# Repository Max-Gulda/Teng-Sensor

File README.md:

# TENG Sensor Scope

This repository contains two parts:

- `nrf54/`: Zephyr firmware for the Nordic **nRF54L15 DK target** (`nrf54l15dk/nrf54l15/cpuapp`) used by the course board setup
- `gui/`: a Python BLE scope GUI that displays calibrated ADS131M04 voltage streams

Minimal Zephyr RTOS firmware intended for the course proprietary board setup. The Zephyr build target used for this course setup is:

- `nrf54l15dk/nrf54l15/cpuapp`

The firmware samples **ADS131M04** 24-bit ADC data. All 4 ADC channels are enabled and streamed over BLE as signed raw counts. CH0 and CH1 are intended to be displayed as source voltage through the 100k/15k input dividers; CH2 and CH3 are direct ADC input voltage.

It transmits data over **Bluetooth LE** using custom GATT characteristics plus Nordic UART Service (NUS) for logs and scope commands.

## Attribution

Created by:

- **Jesper Sjöberg** — GitHub: [@repsejs](https://github.com/repsejs) — KTH: **@jessjobe**
- **Max Gulda** — GitHub: [@Max-Gulda](https://github.com/Max-Gulda) — KTH: **@gulda**

## Architecture

### Threads and priorities

| Thread | Priority | What it does | Key code |
|---|---:|---|---|
| Sampling | 5 | Reads ADC on ADS131M04 DRDY falling edges and queues data to BLE | `nrf54/src/sampling/sampling.c` |
| Bluetooth | 7 | Batches and transmits ADC notifications; manages connect/disconnect | `nrf54/src/bluetooth/bluetooth.c`, `nrf54/src/bluetooth/bt_*.c` |
| Main | default | Initialization + periodic CPU load logging | `nrf54/src/main.c` |

### Data flow

```text
ADS131M04 CH0-CH3 ─► sampling_thread ───────────────────────────────────────────────► BLE ADC channel (batched notifications)
LOG_* / printk ─────────────────────────────► NUS (BLE log backend)
```

### Source layout (firmware)

- `nrf54/src/ads131m04_spi/` — ADS131M04 SPI driver + configuration
- `nrf54/src/sampling/` — DRDY-driven sampling thread, queues ADC frames to BLE
- `nrf54/src/bluetooth/` — BLE GATT services, batching, queues, and notifications
- `nrf54/src/ble_log_backend/` — routes Zephyr `LOG_*` output over BLE (NUS)

### ADS131M04 notes

- The old `ads131m02_spi` module was renamed to `ads131m04_spi`.
- The driver parses 4 ADC channels and exposes CH0, CH1, CH2, and CH3 in `ads131m04_data_t`.
- The default setup in `ads131m04_full_setup()` enables all four channels.
- CH0 and CH1 have 100k/15k dividers and are converted to source voltage in the GUI.
- CH2 and CH3 have no divider and are converted to direct ADC input voltage in the GUI.
- The main custom BLE ADC payload carries timestamp + CH0 + CH1 + CH2 + CH3.
- Sampling is driven by the ADS131M04 DRDY pin. The default ADC OSR is 8192 (500 SPS), and the GUI can switch among the standard ADS131M04 output data rates.

## Build and run (VS Code + nRF Connect extension)

### Important (VS Code workspace)

When using the **nRF Connect for VS Code** extension, make sure the **opened workspace folder is `nrf54/`** (not the repo root). Otherwise the extension may not detect the application correctly.

### Prerequisites

- VS Code
- **nRF Connect for VS Code** extension installed (Nordic Semiconductor)
- A working nRF Connect SDK toolchain (the extension can install/manage this)
- The **course proprietary board** connected over USB (uses the nRF54L15 DK target)

### Open the project

1. Open this folder in VS Code.
2. In the nRF Connect sidebar:
   - Select the **application**: `nrf54/`
   - Select the board: `nrf54l15dk/nrf54l15/cpuapp`.

### Build

Use the nRF Connect extension’s **Build** action. This project uses Zephyr sysbuild (MCUboot enabled), matching:

```bash
cd nrf54
west build -b nrf54l15dk/nrf54l15/cpuapp --sysbuild
```

### Flash

Use the nRF Connect extension’s **Flash** action, or from a terminal:

```bash
west flash
```

### View logs / verify it runs

You have two common options:

- **UART/serial logs**: use the extension’s serial monitor, or:

```bash
west espresso
```

- **BLE logs over NUS**: connect with a NUS-capable client and view logs streamed by the BLE log backend (enabled in `nrf54/src/main.c`).

## IntelliSense note (students)

This repo is configured to work with VS Code’s **C/C++ IntelliSense**. For full, correct include paths/macros, build once so Zephyr generates:

- `nrf54/build/compile_commands.json`

After the first build, IntelliSense should work.

## Bluetooth DFU (nRF Device Manager)

After building, the build directory will contain a DFU package:

- `nrf54/build/dfu_application.zip`

To flash **over Bluetooth** using the **nRF Device Manager** mobile app:

1. Flash once over USB initially (so the device has the bootloader + BLE DFU enabled).
2. Power the device and connect to it in **nRF Device Manager**.
3. Choose **DFU / Update firmware** (wording varies by app version).
4. Select `dfu_application.zip` and start the update.
5. Wait for the device to reboot and reconnect.

## GUI (Python)

To run the BLE scope GUI:

```bash
cd gui
uv sync
uv run teng-sensor-scope
```

Use **Settings** in the GUI to choose visible channels and plot window length.

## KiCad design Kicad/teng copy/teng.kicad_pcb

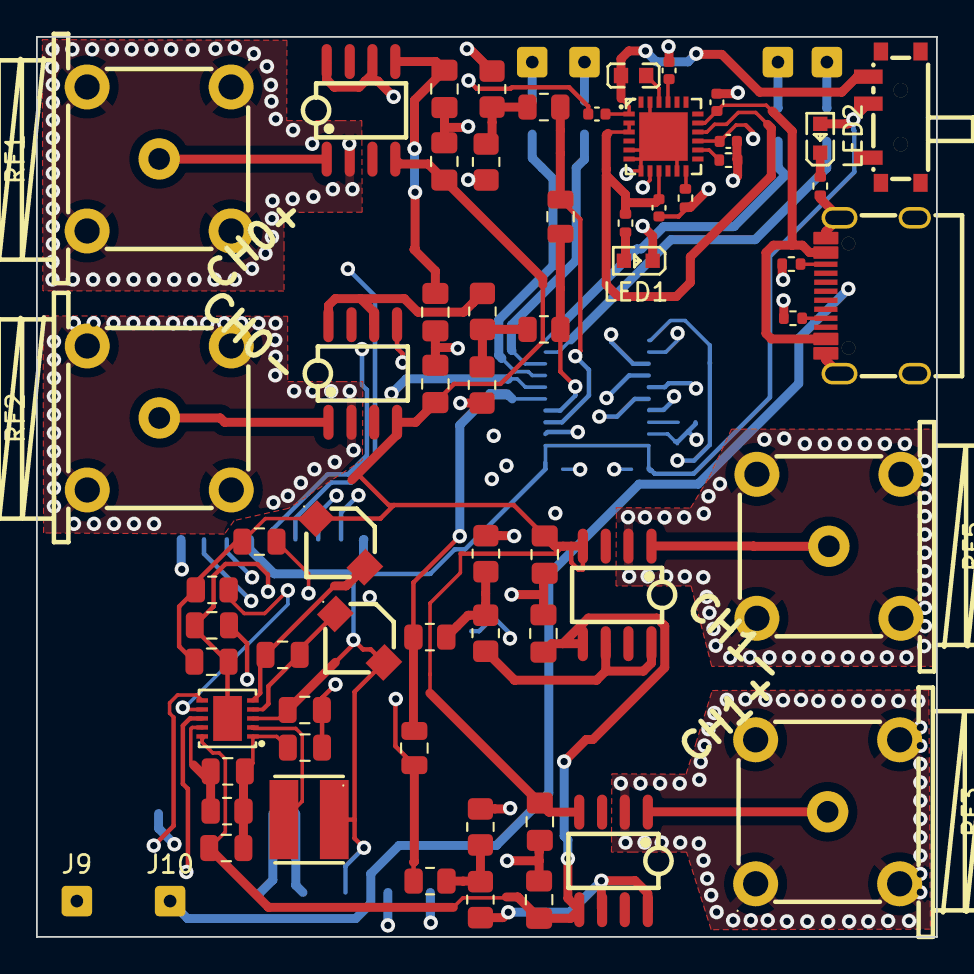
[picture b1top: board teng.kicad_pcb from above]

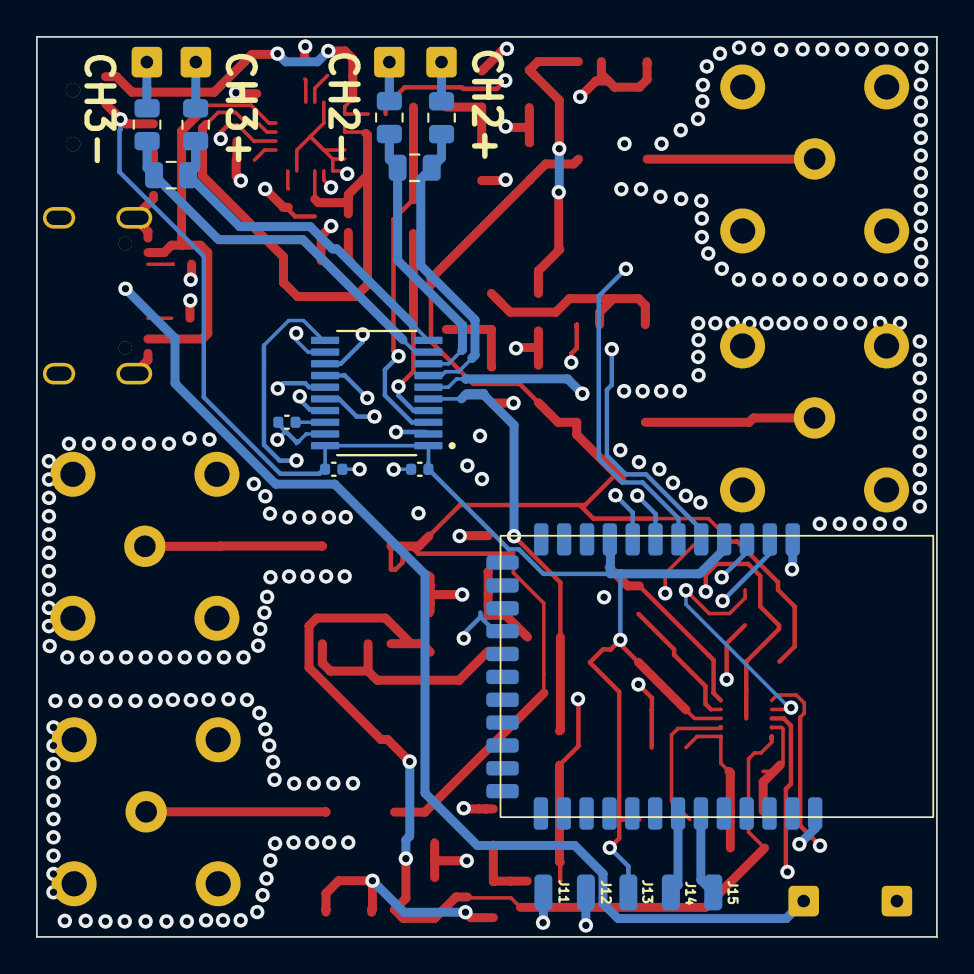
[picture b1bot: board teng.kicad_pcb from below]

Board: 4 copper layers, 50.0 x 50.0 mm, 83 parts (20 on the bottom side), 62 nets.

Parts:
C1, C2, C19, C20: 10nF; C_0805_2012Metric
C3, C4, C5, C6, C15, C16, C17, C18: 100nF; C_0805_2012Metric_Pad1.18x1.45mm_HandSolder
C7, C9: 10uF; C_0402_1005Metric
C8: 2.2uF; C_0402_1005Metric
C10, C12, C14: 1uF; C_0402_1005Metric
C11: 220nF; C_0402_1005Metric
C13: 22uF; C_0402_1005Metric
C21: 33pF; C_0805_2012Metric
C22, C25: 100nF; C_0805_2012Metric
C23: 15pF; C_0805_2012Metric
C24: 4.7uF; C_0805_2012Metric
C26: 22uF; C_0805_2012Metric
C27: 1uF; C_0805_2012Metric
C28: 2.2uF; C_0805_2012Metric
J5: AIN1N-input; SolderWire-0.15sqmm_1x01_D0.5mm_OD1.5mm
J6, J7, J8: AIN1N-input; SolderWire-0.127sqmm_1x01_D0.48mm_OD1mm
J9, J10: Conn_01x01_Pin; SolderWire-0.127sqmm_1x01_D0.48mm_OD1mm
J11, J12: GND; SolderWirePad_1x01_SMD_1x2mm
J13: VDD; SolderWirePad_1x01_SMD_1x2mm
J14: SWDCLK; SolderWirePad_1x01_SMD_1x2mm
J15: SWDIO; SolderWirePad_1x01_SMD_1x2mm
L1: SDFL1608Q2R2KTF; L0603
L2, L3: CDRH3D23NP-150MC; IND-SMD_L3.8-W3.8_CDRH3D23NP
LED1, LED2: Blue light 0603; LED0603-RD
R1, R7, R9, R16: 100k; R_0805_2012Metric_Pad1.20x1.40mm_HandSolder
R2, R3, R4, R5, R18, R19, R20, R21: 1k; R_0805_2012Metric
R6, R8, R15, R17: 15k; R_0805_2012Metric_Pad1.20x1.40mm_HandSolder
R10, R11: 5k1; R_0402_1005Metric
R12: 1k5; R_0402_1005Metric
R13: 10k; R_0402_1005Metric
R14: 4k7; R_0402_1005Metric
R22: 1k; R_0402_1005Metric
R23: 549k; R_0805_2012Metric
R24: 324k; R_0805_2012Metric
RF1, RF2, RF3, RF5: DOSIN-801-0080; BNC-TH_DOSIN-801-0080
SW1: XDMK-12C01-25; SW-SMD_XDMK-12C01-25
U1, U6, U7, U8: ADA4530-1ARZ-R7; SOIC-8_L5.0-W4.0-P1.27-LS6.0-BL
U3: holyIOT
U4: NPM1100-QDAA-R; QFN-24_L4.0-W4.0-P0.50-TL-EP2.7
U5: ADS131M04IPWR; SOP65P640X120-20N
U9: LT3487EDD#PBF; DFN-10_L3.0-W3.0-P0.50-BL-EP-3
U10: CDRH3D16-100; IND-SMD_L3.8-W3.8_YPRH3D16
USBC1: TYPE-C-31-M-12; USB-C_SMD-TYPE-C-31-M-12_1

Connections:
AIN0N: C2.2, R5.2, U5.4 (AIN0N)
AIN0P: C2.1, R4.2, U5.3 (AIN0P)
AIN1N: C1.2, R3.2, U5.5 (AIN1N)
AIN1P: C1.1, R2.2, U5.6 (AIN1P)
AIN2N: C19.2, R19.2, U5.8 (AIN2N)
AIN2P: C19.1, R18.2, U5.7 (AIN2P)
AIN3N: C20.2, R21.2, U5.9 (AIN3N)
AIN3P: C20.1, R20.2, U5.10 (AIN3P)
CHG: LED1.1 (K), U4.8 (CHG)
CLKIN: U3.16 (P1.08), U5.17 (CLKIN)
CS: U3.6 (P1.12), U5.12 (~CS)
DIN: U3.7 (P1.13), U5.16 (DIN)
DOUT: U3.8 (P1.14), U5.15 (DOUT)
DRDY: U3.2 (P1.09), U5.13 (~DRDY)
GRD0N: RF2.1, RF2.2, RF2.3, RF2.4, U7.2 (GRD)
GRD0P: RF1.1, RF1.2, RF1.3, RF1.4, U6.2 (GRD)
GRD1N: RF5.1, RF5.2, RF5.3, RF5.4, U1.2 (GRD)
GRD1P: RF3.1, RF3.2, RF3.3, RF3.4, U8.2 (GRD)
unnamed: J5.1, R18.1
unnamed: J6.1, R19.1
unnamed: J7.1, R20.1
unnamed: J8.1, R21.1
unnamed: LED1.2 (A), R22.1
unnamed: LED2.1 (K), R14.1
unnamed: R1.2, R5.1, R6.1
unnamed: R4.1, R7.2, R8.1
unnamed: R3.1, R9.2, R15.1
unnamed: R2.1, R16.2, R17.1
unnamed: RF5.5, U1.1 (+IN)
unnamed: R9.1, U1.6 (OUT), U1.8 (–IN)
unnamed: C9.1, U4.21 (DEC)
unnamed: R12.2, U4.12 (ICHG)
unnamed: R13.2, U4.14 (NTC)
unnamed: L1.2, U4.22 (SW)
unnamed: C11.1, U5.18 (CAP)
unnamed: RF1.5, U6.1 (+IN)
unnamed: R7.1, U6.6 (OUT), U6.8 (–IN)
unnamed: RF2.5, U7.1 (+IN)
unnamed: R1.1, U7.6 (OUT), U7.8 (–IN)
unnamed: RF3.5, U8.1 (+IN)
unnamed: R16.1, U8.6 (OUT), U8.8 (–IN)
unnamed: C23.1, C24.1, C25.1, R23.1, U9.1 (CAP)
unnamed: C28.2, L3.2, U9.5 (DN)
unnamed: C21.2, R24.2, U9.7 (FBN)
unnamed: C23.2, R23.2, U9.9 (FBP)
unnamed: C22.1, U9.8 (RUN/SS)
unnamed: C28.1, L2.1, U9.4 (SWN)
unnamed: U9.2 (SWP), U10.2
unnamed: R11.1, USBC1.A5 (CC1)
unnamed: R10.1, USBC1.B5 (CC2)
SCLK: U3.5 (P1.11), U5.14 (SCLK)
SWDCLK: J14.1, U3.30 (SWDCLK)
SWDIO: J15.1, U3.31 (SWDIO)
SYNC/RESET: U3.3 (P1.10), U5.11 (~SYNC/~RESET)
VBUS: C8.2, U4.17 (VBUS), USBC1.A4B9 (VBUS), USBC1.B4A9 (VBUS)
VDD: C12.1, C14.1, C27.1, J13.1, L2.2, LED2.2 (A), SW1.2, U3.4 (VDD), U3.9 (VDDM), U5.1 (AVDD), U5.20 (DVDD), U9.3 (VBAT), U9.6 (VIN), U10.1
VNEG: C3.1, C5.1, C6.1, C16.1, C21.1, C26.1, L3.1, R24.1, U1.4 (V–), U6.4 (V–), U7.4 (V–), U8.4 (V–)
VOUT: C7.1, L1.1, SW1.1, U4.1 (VOUTB)
VPOS: C4.1, C15.1, C17.1, C18.1, C25.2, U1.5 (V+), U6.5 (V+), U7.5 (V+), U8.5 (V+), U9.10 (VPOS)
VSYS: C13.1, R22.2, U4.2 (VOUTBSET1), U4.3 (VOUTBSET2), U4.9 (VTERMSET), U4.16 (VSYS)
bat+: C10.1, J10.1, U4.15 (VBAT)
bat-: C3.2, C4.2, C5.2, C6.2, C7.2, C8.1, C9.2, C10.2, C11.2, C12.2, C13.2, C14.2, C15.2, C16.2, C17.2, C18.2, C22.2, C24.2, C26.2, C27.2, J9.1, J11.1, J12.1, R6.2, R8.2, R10.2, R11.2, R12.1, R13.1, R14.2, R15.2, R17.2, U3.1 (GND), U3.36 (GND), U4.5 (ISET), U4.6 (SHPACT), U4.7 (MODE), U4.11 (SHPHLD), U4.23 (PVSS), U4.25 (EP), U5.2 (AGND), U5.19 (DGND), U9.11 (GND), USBC1.1 (EH), USBC1.2 (EH), USBC1.3 (EH), USBC1.4 (EH), USBC1.A1B12 (GND), USBC1.B1A12 (GND)

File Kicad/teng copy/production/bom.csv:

Designator,Footprint,Quantity,Value,LCSC Part #
"C1, C19, C2, C20",0805,4,10nF,
"C10, C12, C14",0402,3,1uF,
C11,0402,1,220nF,
C13,0402,1,22uF,
"C15, C16, C17, C18, C22, C25, C3, C4, C5, C6",0805,10,100nF,
C21,0805,1,33pF,
C23,0805,1,15pF,
C24,0805,1,4.7uF,
C26,0805,1,22uF,
C27,0805,1,1uF,
C28,0805,1,2.2uF,
"C7, C9",0402,2,10uF,
C8,0402,1,2.2uF,
"J10, J9",SolderWire-0.127sqmm_1x01_D0.48mm_OD1mm,2,Conn_01x01_Pin,
"J11, J12",SolderWirePad_1x01_SMD_1x2mm,2,GND,
J13,SolderWirePad_1x01_SMD_1x2mm,1,VDD,
J14,SolderWirePad_1x01_SMD_1x2mm,1,SWDCLK,
J15,SolderWirePad_1x01_SMD_1x2mm,1,SWDIO,
J5,SolderWire-0.15sqmm_1x01_D0.5mm_OD1.5mm,1,AIN1N-input,
"J6, J7, J8",SolderWire-0.127sqmm_1x01_D0.48mm_OD1mm,3,AIN1N-input,
L1,L0603,1,SDFL1608Q2R2KTF,C1033
"L2, L3",IND-SMD_L3.8-W3.8_CDRH3D23NP,2,CDRH3D23NP-150MC,C323529
"LED1, LED2",LED0603-RD,2,Blue light 0603,C2288
"R1, R16, R7, R9",0805,4,100k,
"R10, R11",0402,2,5k1,
R12,0402,1,1k5,
R13,0402,1,10k,
R14,0402,1,4k7,
"R15, R17, R6, R8",0805,4,15k,
"R18, R19, R2, R20, R21, R3, R4, R5",0805,8,1k,
R22,0402,1,1k,
R23,0805,1,549k,
R24,0805,1,324k,
"RF1, RF2, RF3, RF5",BNC-TH_DOSIN-801-0080,4,DOSIN-801-0080,C521219
SW1,SW-SMD_XDMK-12C01-25,1,XDMK-12C01-25,C7498220
"U1, U6, U7, U8",SOIC-8_L5.0-W4.0-P1.27-LS6.0-BL,4,ADA4530-1ARZ-R7,C77380
U10,IND-SMD_L3.8-W3.8_YPRH3D16,1,CDRH3D16-100,C9900018502
U3,holyIOT,1,~,
U4,QFN-24_L4.0-W4.0-P0.50-TL-EP2.7,1,NPM1100-QDAA-R,C5816773
U5,SOP65P640X120-20N,1,ADS131M04IPWR,
U9,DFN-10_L3.0-W3.0-P0.50-BL-EP-3,1,LT3487EDD#PBF,C580078
USBC1,USB-C_SMD-TYPE-C-31-M-12_1,1,TYPE-C-31-M-12,C165948

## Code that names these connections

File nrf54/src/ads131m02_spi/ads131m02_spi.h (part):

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typedef struct {
    const struct device *spi_dev;
    struct spi_config spi_cfg;
    struct gpio_dt_spec drdy_gpio;
    struct gpio_dt_spec reset_gpio;
} ads131m02_config_t;

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#define ADS131M02_REGMASK_GAIN_PGAGAIN0  0x0007

/* Input channel mux options */
#define ADS131M02_MUX_AIN_DIFFERENTIAL   0  /* Default: AIN0P-AIN0N */
#define ADS131M02_MUX_INPUT_SHORTED      1
#define ADS131M02_MUX_POSITIVE_DC_TEST   2
#define ADS131M02_MUX_NEGATIVE_DC_TEST   3
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int ads131m02_reset_release(ads131m02_config_t *config);

/**
 * @brief Check if DRDY pin is low
 * @param config Pointer to device configuration
 * @return 1 if DRDY is low, 0 if high, negative on error
 */
int ads131m02_drdy_is_low(ads131m02_config_t *config);

/**
 * @brief Wait for DRDY pin to go low (falling edge)
 * @param config Pointer to device configuration
 * @param timeout_us Timeout in microseconds
 * @return 0 if DRDY went low, -ETIMEDOUT on timeout, negative on other errors
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
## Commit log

2026-03-27 docs: clarify VS Code workspace and GUI toolkit
    Explain that nRF Connect VS Code should open the nrf54/ folder, and note the GUI uses Qt (PySide6).
2026-03-27 gui: add Qt/pyqtgraph deps and uv lockfile
    Add PySide6 + pyqtgraph and configure hatchling build metadata so the gui runs via uv with a reproducible lock.
2026-03-27 gui: implement BLE streaming Qt app
    Use PySide6 + pyqtgraph with threaded BLE scan/streaming, device dropdown selection, stacked plots, NUS log forwarding to terminal, and basic ECG conditioning toggles.
2026-03-27 chore: untrack local CLAUDE instructions
    Stop tracking nrf54/CLAUDE.md and add it to .gitignore.
2026-03-27 gui: remove unused log panel
    Logs are printed to stdout, so drop the in-window log label and text box.
2026-04-08 new optuna params
2026-04-08 firmware: migrate ADC path to ADS131M04
2026-04-08 gui: show ADS131M04 channel streams
2026-04-08 firmware: update gain settings to use user-facing multipliers and add gain conversion function, fixed read_register bug
2026-04-08 refactor: clean up code formatting and improve error logging for ADC and IMU reads
2026-05-20 Update TENG sensor firmware and data collector
2026-06-04 Improve BLE scope controls and recording
2026-06-04 made it force use of cpython3.13
2026-06-04 Polish scope UI theme and recordings
2026-06-04 changed to interrupt driven
2026-06-04 Add SVG asset for Teng Sensor Scope visualization
